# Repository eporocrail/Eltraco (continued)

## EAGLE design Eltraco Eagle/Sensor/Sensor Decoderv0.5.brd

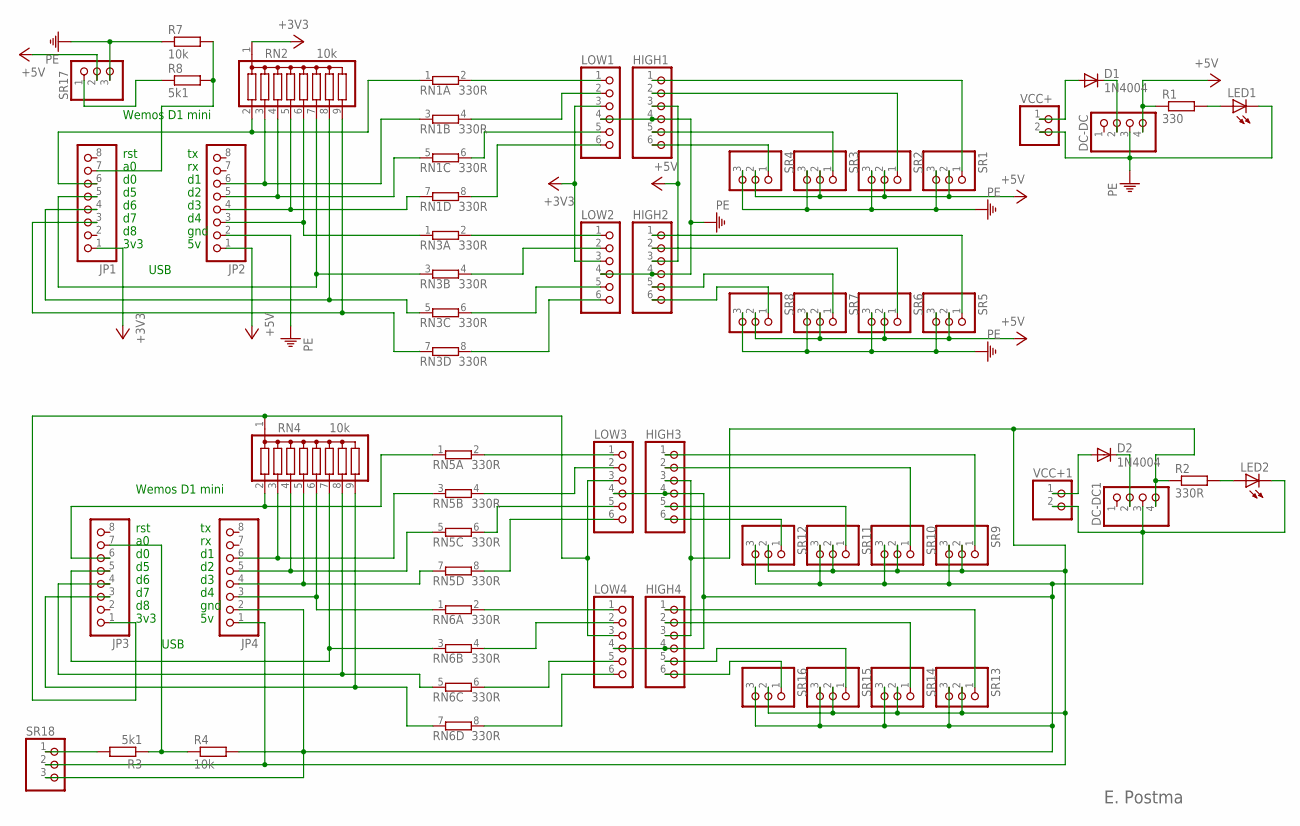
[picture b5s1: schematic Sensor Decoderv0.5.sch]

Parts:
D1, D2: 1N4004; DO41-10
DC-DC, DC-DC1: PINHD-1X4; 1X04
HIGH1, HIGH2, HIGH3, HIGH4: PINHD-1X6; 1X06
JP1, JP2, JP3, JP4: PINHD-1X8; 1X08
LED1, LED2: LED3MM
LOW1, LOW2, LOW3, LOW4: PINHD-1X6; 1X06
R1: 330; 0207/7
R2: 330R; 0207/7
R3, R8: 5k1; 0207/7
R4, R7: 10k; 0207/7
RN1, RN3, RN5, RN6: 330R; SIL8
RN2, RN4: 10k; SIL9
SR1, SR2, SR3, SR4, SR5, SR6, SR7, SR8, SR9, SR10, SR11, SR12, SR13, SR14, SR15, SR16, SR17, SR18: PINHD-1X3; 1X03
VCC+, VCC+1: PINHD-1X2; 1X02

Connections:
+3V3: JP1.1, LOW1.3, LOW2.3, RN2.1
+5V: DC-DC.4, HIGH1.3, HIGH2.3, JP2.1, R1.1, SR1.2, SR2.2, SR3.2, SR4.2, SR5.2, SR6.2, SR7.2, SR8.2, SR17.2
unnamed: HIGH2.6, SR8.1
unnamed: JP1.6, RN1.1, RN2.2
unnamed: JP1.4, RN2.8, RN3.5 (1)
unnamed: D1.C, DC-DC.2
unnamed: JP1.5, RN2.7, RN3.3 (1)
unnamed: LED1.A, R1.2
unnamed: JP2.5, RN1.5 (1), RN2.4
unnamed: HIGH2.5, SR7.1
unnamed: JP2.3, RN2.6, RN3.1
unnamed: JP2.6, RN1.3 (1), RN2.3
unnamed: JP1.3, RN2.9, RN3.7 (1)
unnamed: LOW1.1, RN1.2
unnamed: JP2.4, RN1.7 (1), RN2.5
unnamed: HIGH1.6, SR4.1
unnamed: HIGH1.5, SR3.1
unnamed: HIGH1.2, SR2.1
unnamed: HIGH1.1, SR1.1
unnamed: HIGH2.2, SR6.1
unnamed: HIGH2.1, SR5.1
unnamed: JP3.6, RN4.2, RN5.1
unnamed: LED2.A, R2.2
unnamed: JP4.6, RN4.3, RN5.3 (1)
unnamed: JP4.5, RN4.4, RN5.5 (1)
unnamed: JP4.4, RN4.5, RN5.7 (1)
unnamed: D2.A, VCC+1.1
unnamed: D2.C, DC-DC1.2
unnamed: JP4.3, RN4.6, RN6.1
unnamed: JP3.5, RN4.7, RN6.3 (1)
unnamed: JP3.4, RN4.8, RN6.5 (1)
unnamed: JP3.3, RN4.9, RN6.7 (1)
unnamed: LOW3.1, RN5.2
unnamed: LOW3.2, RN5.4 (2)
unnamed: LOW3.5, RN5.6 (2)
unnamed: LOW3.6, RN5.8 (2)
unnamed: LOW4.1, RN6.2
unnamed: LOW4.2, RN6.4 (2)
unnamed: LOW4.5, RN6.6 (2)
unnamed: LOW4.6, RN6.8 (2)
unnamed: HIGH4.6, SR16.1
unnamed: HIGH4.5, SR15.1
unnamed: HIGH4.2, SR14.1
unnamed: HIGH4.1, SR13.1
unnamed: HIGH3.6, SR12.1
unnamed: LOW1.2, RN1.4 (2)
unnamed: LOW1.5, RN1.6 (2)
unnamed: LOW1.6, RN1.8 (2)
unnamed: D1.A, VCC+.1
unnamed: LOW2.1, RN3.2
unnamed: LOW2.2, RN3.4 (2)
unnamed: LOW2.5, RN3.6 (2)
unnamed: LOW2.6, RN3.8 (2)
unnamed: HIGH3.5, SR11.1
unnamed: HIGH3.2, SR10.1
unnamed: HIGH3.1, SR9.1
unnamed: DC-DC1.4, HIGH3.3, HIGH4.3, JP4.1, R2.1, SR9.2, SR10.2, SR11.2, SR12.2, SR13.2, SR14.2, SR15.2, SR16.2, SR18.2
unnamed: JP3.1, LOW3.3, LOW4.3, RN4.1
unnamed: DC-DC1.3, HIGH3.4, HIGH4.4, JP4.2, LED2.K (C), LOW3.4, LOW4.4, R4.2, SR9.3, SR10.3, SR11.3, SR12.3, SR13.3, SR14.3, SR15.3, SR16.3, SR18.3, VCC+1.2
unnamed: JP1.7, R7.2, R8.2
unnamed: JP3.7, R3.1, R4.1
unnamed: R3.2, SR18.1
unnamed: R8.1, SR17.1
PE: DC-DC.3, HIGH1.4, HIGH2.4, JP2.2, LED1.K (C), LOW1.4, LOW2.4, R7.1, SR1.3, SR2.3, SR3.3, SR4.3, SR5.3, SR6.3, SR7.3, SR8.3, SR17.3, VCC+.2

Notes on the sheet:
rst
3v3
Wemos D1 mini
gnd
USB
E. Postma

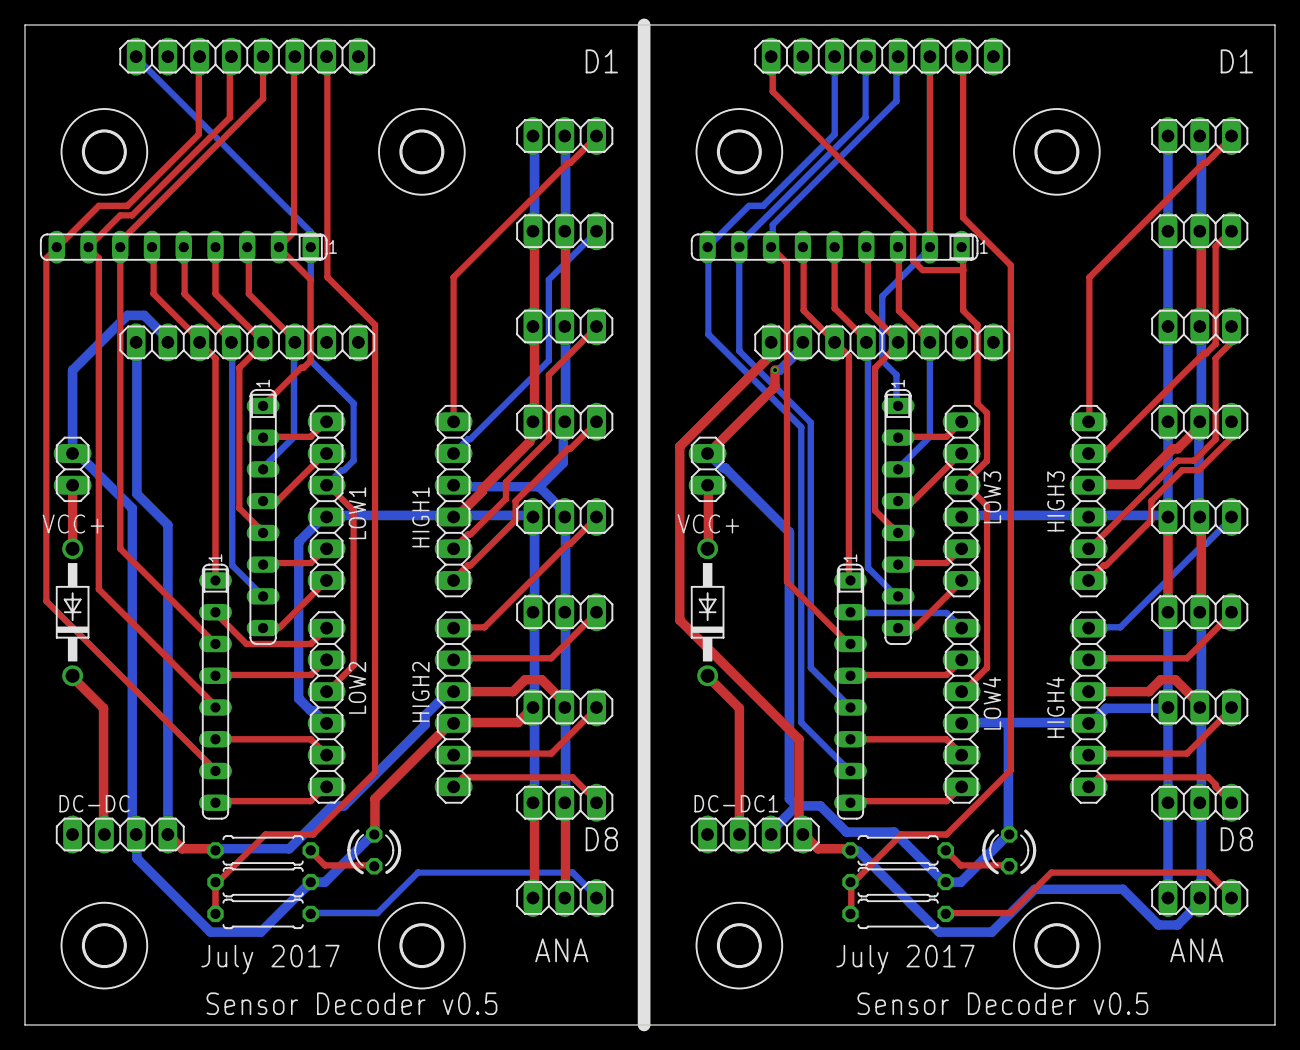
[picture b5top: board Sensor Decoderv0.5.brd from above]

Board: 2 copper layers, 100.0 x 80.0 mm, 58 parts (0 on the bottom side), 64 nets.

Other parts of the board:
U$1, U$2, U$3, U$4, U$5, U$6, U$7, U$8: 3,2

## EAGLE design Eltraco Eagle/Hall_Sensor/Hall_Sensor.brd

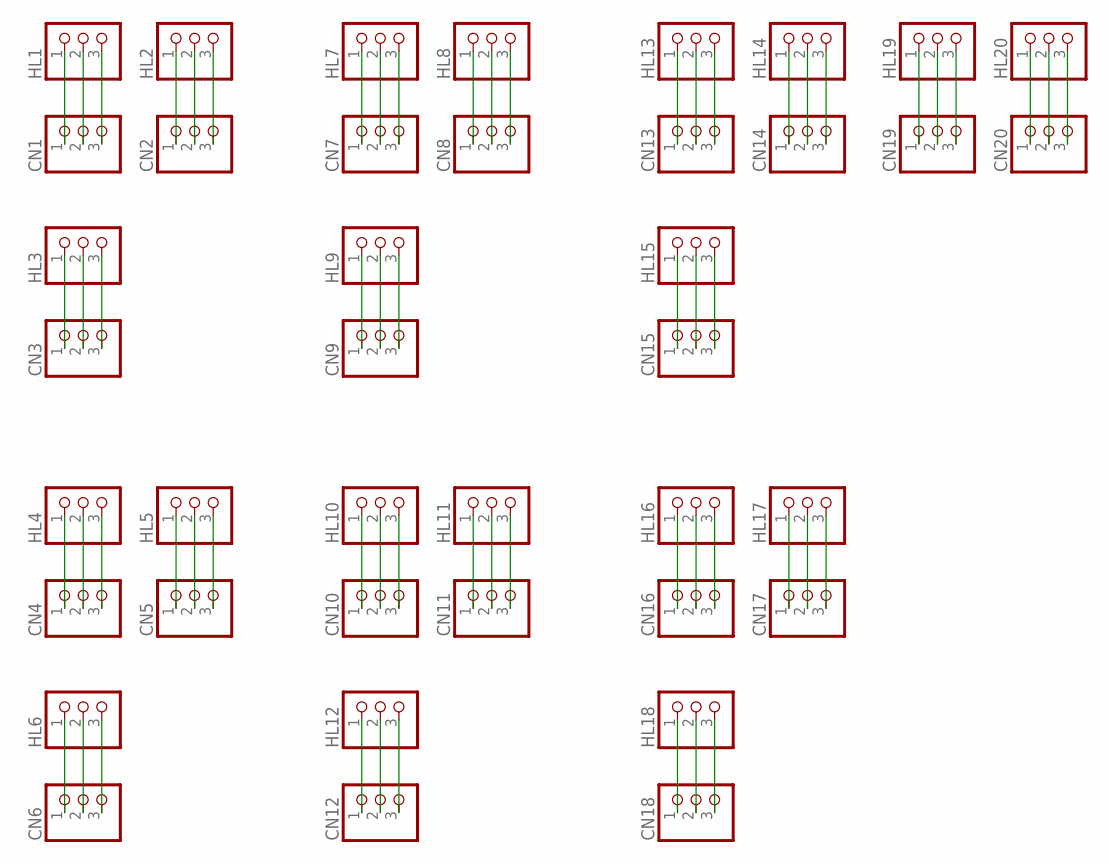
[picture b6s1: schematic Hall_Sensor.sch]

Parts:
CN1, CN2, CN3, CN4, CN5, CN6, CN7, CN8, CN9, CN10, CN11, CN12, CN13, CN14, CN15, CN16, CN17, CN18, CN19, CN20: PINHD-1X3; 1X03
HL1, HL2, HL3, HL4, HL5, HL6, HL7, HL8, HL9, HL10, HL11, HL12, HL13, HL14, HL15, HL16, HL17, HL18, HL19, HL20: PINHD-1X3; 1X03

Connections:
unnamed: CN7.1, HL7.1
unnamed: CN7.2, HL7.2
unnamed: CN7.3, HL7.3
unnamed: CN8.1, HL8.1
unnamed: CN8.2, HL8.2
unnamed: CN8.3, HL8.3
unnamed: CN9.1, HL9.1
unnamed: CN9.2, HL9.2
unnamed: CN9.3, HL9.3
unnamed: CN10.1, HL10.1
unnamed: CN10.2, HL10.2
unnamed: CN10.3, HL10.3
unnamed: CN11.1, HL11.1
unnamed: CN11.2, HL11.2
unnamed: CN11.3, HL11.3
unnamed: CN12.1, HL12.1
unnamed: CN12.2, HL12.2
unnamed: CN12.3, HL12.3
unnamed: CN13.1, HL13.1
unnamed: CN13.2, HL13.2
unnamed: CN13.3, HL13.3
unnamed: CN14.1, HL14.1
unnamed: CN14.2, HL14.2
unnamed: CN14.3, HL14.3
unnamed: CN15.1, HL15.1
unnamed: CN15.2, HL15.2
unnamed: CN15.3, HL15.3
unnamed: CN16.1, HL16.1
unnamed: CN16.2, HL16.2
unnamed: CN16.3, HL16.3
unnamed: CN17.1, HL17.1
unnamed: CN17.2, HL17.2
unnamed: CN17.3, HL17.3
unnamed: CN18.1, HL18.1
unnamed: CN18.2, HL18.2
unnamed: CN18.3, HL18.3
unnamed: CN19.1, HL19.1
unnamed: CN19.2, HL19.2
unnamed: CN19.3, HL19.3
unnamed: CN1.1, HL1.1
unnamed: CN20.1, HL20.1
unnamed: CN20.2, HL20.2
unnamed: CN20.3, HL20.3
unnamed: CN1.2, HL1.2
unnamed: CN1.3, HL1.3
unnamed: CN2.1, HL2.1
unnamed: CN2.2, HL2.2
unnamed: CN2.3, HL2.3
unnamed: CN3.1, HL3.1
unnamed: CN3.2, HL3.2
unnamed: CN3.3, HL3.3
unnamed: CN4.1, HL4.1
unnamed: CN4.2, HL4.2
unnamed: CN4.3, HL4.3
unnamed: CN5.1, HL5.1
unnamed: CN5.2, HL5.2
unnamed: CN5.3, HL5.3
unnamed: CN6.1, HL6.1
unnamed: CN6.2, HL6.2
unnamed: CN6.3, HL6.3

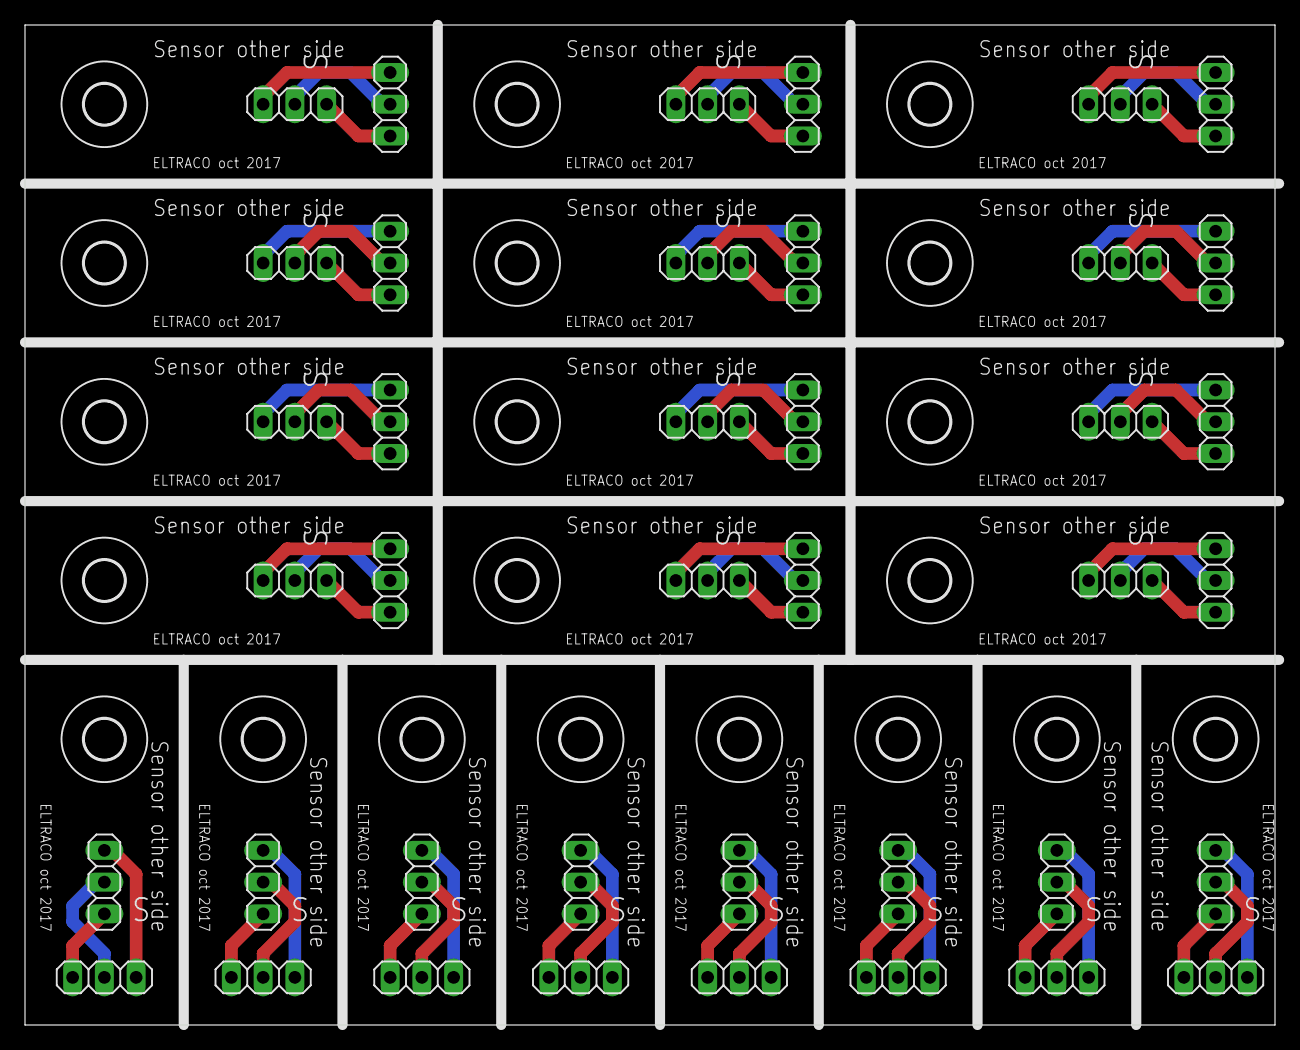
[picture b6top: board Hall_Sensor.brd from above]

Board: 2 copper layers, 100.0 x 80.0 mm, 60 parts (0 on the bottom side), 60 nets.

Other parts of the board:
U$1, U$2, U$3, U$4, U$5, U$6, U$7, U$8, U$9, U$10, U$11, U$12, U$13, U$14, U$15, U$16, U$17, U$18, U$19, U$20: 3,2

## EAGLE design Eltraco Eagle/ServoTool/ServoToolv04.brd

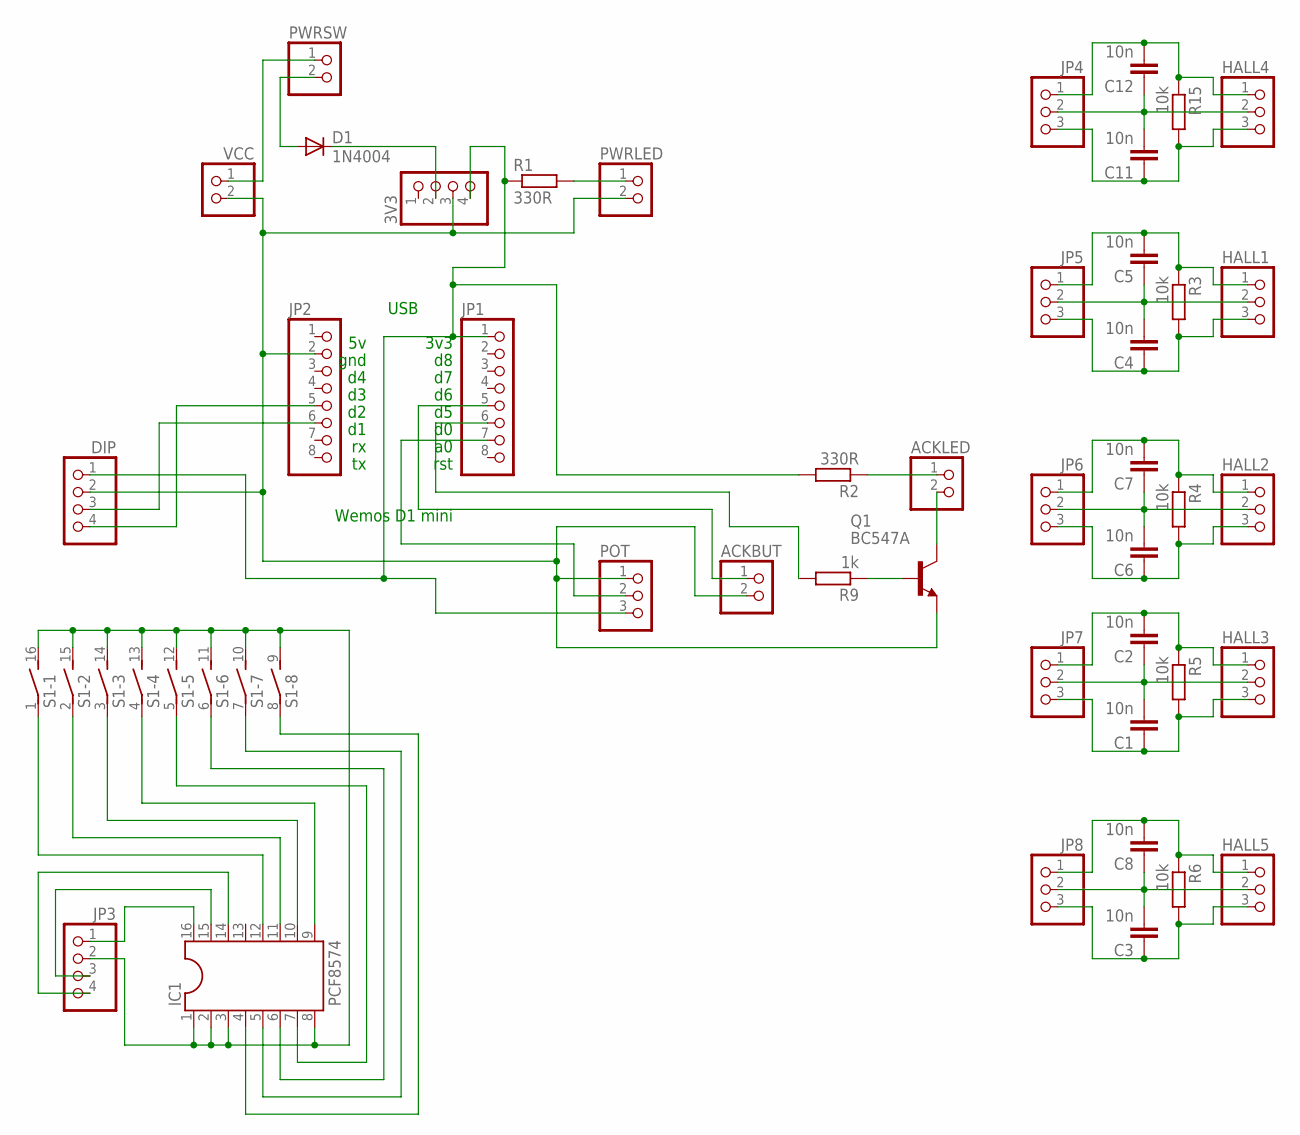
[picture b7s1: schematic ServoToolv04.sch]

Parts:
3V3: PINHD-1X4; 1X04
ACKBUT: PINHD-1X2/90; 1X02/90
ACKLED: PINHD-1X2/90; 1X02/90
C1, C2, C3, C4, C5, C6, C7, C8, C11, C12: 10n; C050-024X044
D1: 1N4004; DO41-10
DIP: PINHD-1X4/90; 1X04/90
HALL1, HALL2, HALL3, HALL4, HALL5: PINHD-1X3; 1X03
IC1: PCF8574; DIL16
JP1, JP2: PINHD-1X8; 1X08
JP3: PINHD-1X4/90; 1X04/90
JP4, JP5, JP6, JP7, JP8: PINHD-1X3; 1X03
POT: PINHD-1X3/90; 1X03/90
PWRLED: PINHD-1X2/90; 1X02/90
PWRSW: PINHD-1X2/90; 1X02/90
Q1: BC547A; TO92
R1, R2: 330R; 0207/10
R3, R4, R5, R6, R15: 10k; 0309/10
R9: 1k; 0207/10
S1: DIP08S
VCC: PINHD-1X2/90; 1X02/90

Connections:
unnamed: 3V3.4, DIP.1, JP1.1, POT.3, R1.1, R2.2
unnamed: DIP.3, JP2.6
unnamed: DIP.4, JP2.5
unnamed: 3V3.2, D1.C
unnamed: PWRSW.1, VCC.1
unnamed: PWRLED.1, R1.2
unnamed: Q1.2 (B), R9.1
unnamed: ACKLED.1, R2.1
unnamed: ACKLED.2, Q1.3 (C)
unnamed: IC1.12, S1.1
unnamed: IC1.11, S1.2 (1)
unnamed: IC1.10, S1.3 (1)
unnamed: IC1.16, JP3.1
unnamed: ACKBUT.1, JP1.5
unnamed: JP1.7, POT.2
unnamed: C5.2, HALL1.1, JP5.1, R3.1
unnamed: JP1.6, R9.2
unnamed: D1.A, PWRSW.2
unnamed: 3V3.3, ACKBUT.2, DIP.2, JP2.2, POT.1, PWRLED.2, Q1.1 (E), VCC.2
unnamed: C4.2, C5.1, HALL1.2, JP5.2
unnamed: IC1.1, IC1.2, IC1.3, IC1.8, JP3.2, S1.9 (2), S1.10 (2), S1.11 (2), S1.12 (2), S1.13 (2), S1.14 (2), S1.15 (2), S1.16 (2)
unnamed: IC1.15, JP3.3
unnamed: IC1.14, JP3.4
unnamed: IC1.9, S1.4 (1)
unnamed: IC1.7, S1.5 (1)
unnamed: IC1.6, S1.6 (1)
unnamed: C4.1, HALL1.3, JP5.3, R3.2
unnamed: C6.2, C7.1, HALL2.2, JP6.2
unnamed: IC1.5, S1.7 (1)
unnamed: C7.2, HALL2.1, JP6.1, R4.1
unnamed: C6.1, HALL2.3, JP6.3, R4.2
unnamed: C1.2, C2.1, HALL3.2, JP7.2
unnamed: C2.2, HALL3.1, JP7.1, R5.1
unnamed: C1.1, HALL3.3, JP7.3, R5.2
unnamed: IC1.4, S1.8 (1)
unnamed: C3.2, C8.1, HALL5.2, JP8.2
unnamed: C8.2, HALL5.1, JP8.1, R6.1
unnamed: C3.1, HALL5.3, JP8.3, R6.2
unnamed: C11.2, C12.1, HALL4.2, JP4.2
unnamed: C11.1, HALL4.3, JP4.3, R15.2
unnamed: C12.2, HALL4.1, JP4.1, R15.1

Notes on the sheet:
rst
3v3
Wemos D1 mini
gnd
USB

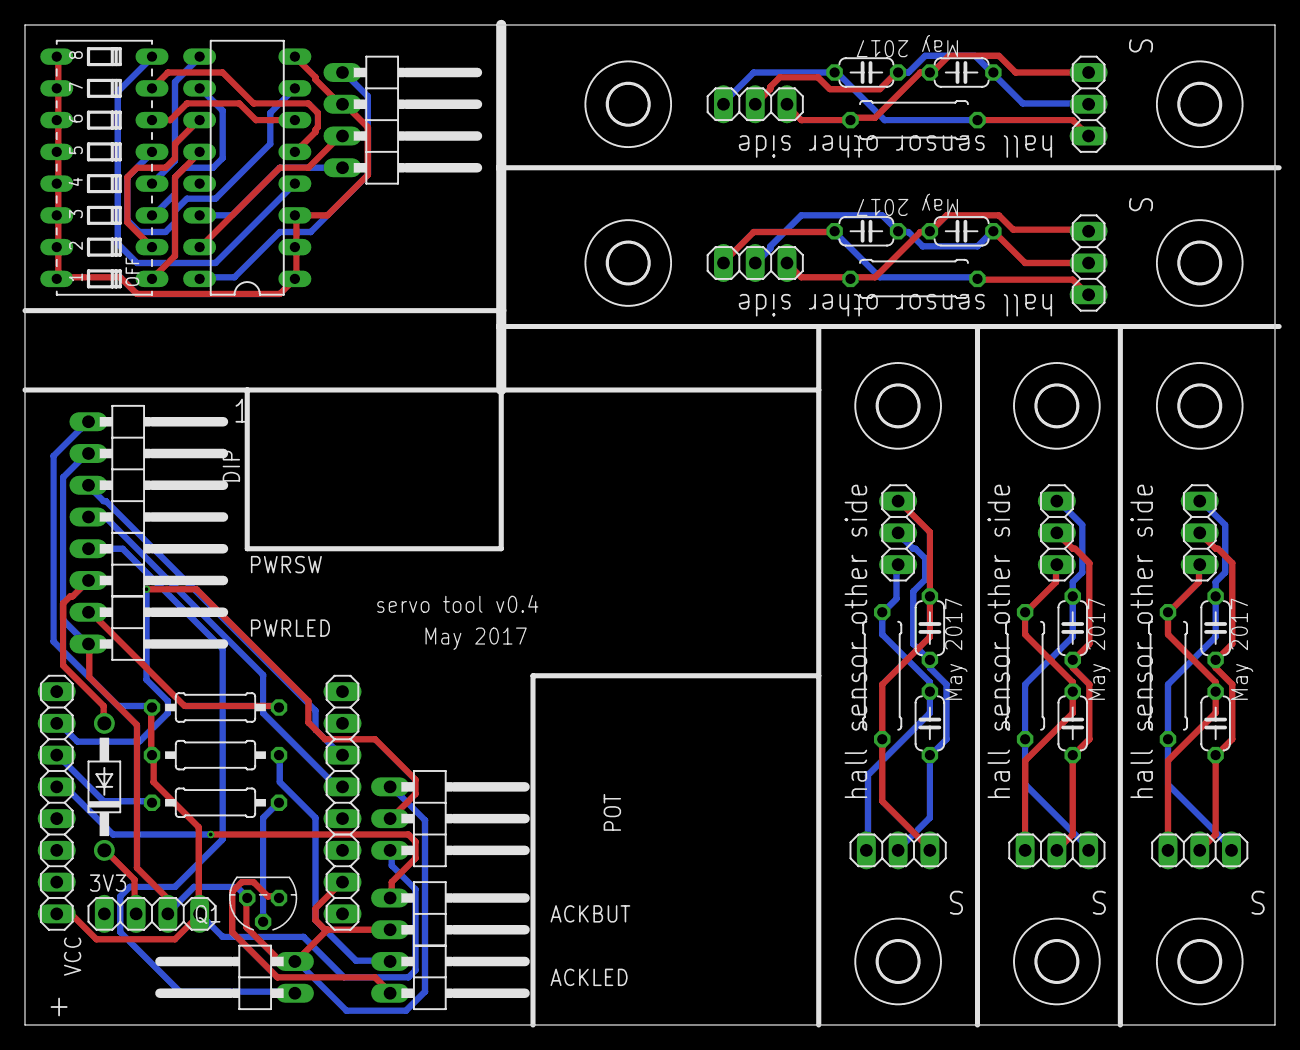
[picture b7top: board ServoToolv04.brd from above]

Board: 2 copper layers, 100.0 x 80.0 mm, 53 parts (0 on the bottom side), 41 nets.

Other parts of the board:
U$1, U$2, U$3, U$4, U$5, U$6, U$7, U$8, U$9, U$10: 3,2

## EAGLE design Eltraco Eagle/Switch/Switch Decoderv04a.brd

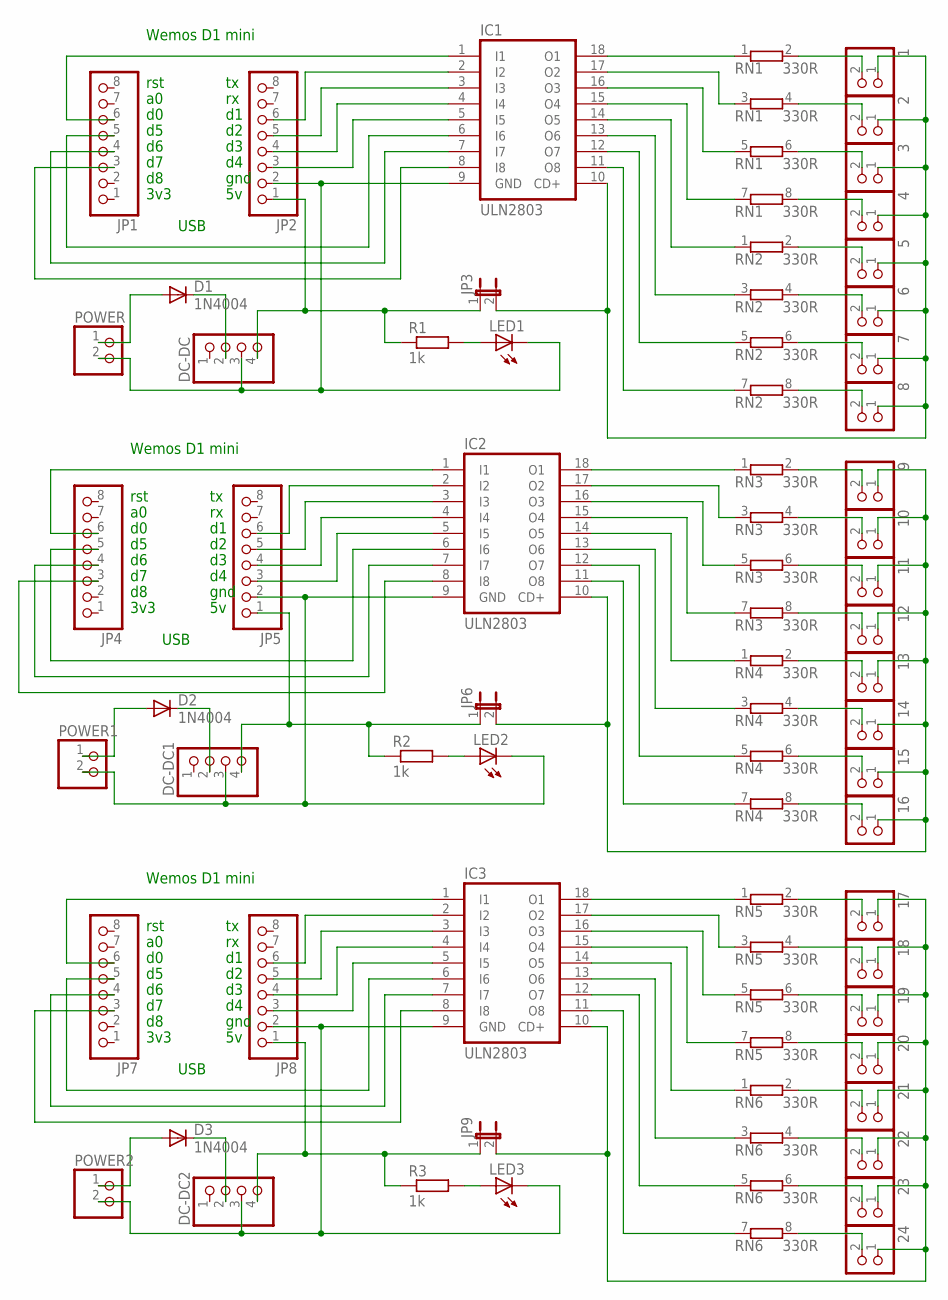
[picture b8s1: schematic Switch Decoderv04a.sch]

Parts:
1, 2, 3, 4, 5, 6, 7, 8, 9, 10, 11, 12, 13, 14, 15, 16, 17, 18, 19, 20, 21, 22, 23, 24: PINHD-1X2; 1X02
D1, D2, D3: 1N4004; DO41-10
DC-DC, DC-DC1, DC-DC2: PINHD-1X4; 1X04
IC1, IC2, IC3: ULN2803; DIL18
JP1, JP2, JP4, JP5, JP7, JP8: PINHD-1X8; 1X08
JP3, JP6, JP9: JP1E; JP1
LED1, LED2, LED3: LED3MM
POWER, POWER1, POWER2: PINHD-1X2; 1X02
R1, R2, R3: 1k; 0309/10
RN1, RN2, RN3, RN4, RN5, RN6: 330R; SIL8

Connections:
unnamed: DC-DC.3, IC1.9 (GND), JP2.2, LED1.K (C), POWER.2
unnamed: IC1.1 (I1), JP1.6
unnamed: IC1.7 (I7), JP1.4
unnamed: D1.C, DC-DC.2
unnamed: IC1.6 (I6), JP1.5
unnamed: LED1.A, R1.2
unnamed: IC1.3 (I3), JP2.5
unnamed: 1.1, 2.1, 3.1, 4.1, 5.1, 6.1, 7.1, 8.1, IC1.10 (CD+), JP3.2
unnamed: IC1.5 (I5), JP2.3
unnamed: IC1.2 (I2), JP2.6
unnamed: IC1.8 (I8), JP1.3
unnamed: IC1.18 (O1), RN1.1
unnamed: IC1.4 (I4), JP2.4
unnamed: IC2.1 (I1), JP4.6
unnamed: 1.2, RN1.2
unnamed: 9.1, 10.1, 11.1, 12.1, 13.1, 14.1, 15.1, 16.1, IC2.10 (CD+), JP6.2
unnamed: IC1.17 (O2), RN1.3 (1)
unnamed: 2.2, RN1.4 (2)
unnamed: 3.2, RN1.6 (2)
unnamed: IC1.16 (O3), RN1.5 (1)
unnamed: IC1.15 (O4), RN1.7 (1)
unnamed: 4.2, RN1.8 (2)
unnamed: 5.2, RN2.2
unnamed: IC1.14 (O5), RN2.1
unnamed: IC1.13 (O6), RN2.3 (1)
unnamed: 6.2, RN2.4 (2)
unnamed: 7.2, RN2.6 (2)
unnamed: IC1.12 (O7), RN2.5 (1)
unnamed: 8.2, RN2.8 (2)
unnamed: LED2.A, R2.2
unnamed: IC2.2 (I2), JP5.6
unnamed: IC2.3 (I3), JP5.5
unnamed: IC2.4 (I4), JP5.4
unnamed: D2.A, POWER1.1
unnamed: D2.C, DC-DC1.2
unnamed: IC2.5 (I5), JP5.3
unnamed: IC2.6 (I6), JP4.5
unnamed: IC2.7 (I7), JP4.4
unnamed: IC2.8 (I8), JP4.3
unnamed: IC3.18 (O1), RN5.1
unnamed: DC-DC1.3, IC2.9 (GND), JP5.2, LED2.K (C), POWER1.2
unnamed: IC1.11 (O8), RN2.7 (1)
unnamed: IC2.11 (O8), RN4.7 (1)
unnamed: IC2.18 (O1), RN3.1
unnamed: IC2.17 (O2), RN3.3 (1)
unnamed: 9.2, RN3.2
unnamed: D1.A, POWER.1
unnamed: 10.2, RN3.4 (2)
unnamed: IC2.16 (O3), RN3.5 (1)
unnamed: IC2.15 (O4), RN3.7 (1)
unnamed: 11.2, RN3.6 (2)
unnamed: 12.2, RN3.8 (2)
unnamed: IC2.14 (O5), RN4.1
unnamed: IC2.13 (O6), RN4.3 (1)
unnamed: 13.2, RN4.2
unnamed: 14.2, RN4.4 (2)
unnamed: IC2.12 (O7), RN4.5 (1)
unnamed: 15.2, RN4.6 (2)
unnamed: IC3.1 (I1), JP7.6
unnamed: LED3.A, R3.2
unnamed: IC3.2 (I2), JP8.6
unnamed: IC3.3 (I3), JP8.5
unnamed: IC3.4 (I4), JP8.4
unnamed: D3.A, POWER2.1
unnamed: D3.C, DC-DC2.2
unnamed: IC3.5 (I5), JP8.3
unnamed: IC3.6 (I6), JP7.5
unnamed: IC3.7 (I7), JP7.4
unnamed: IC3.8 (I8), JP7.3
unnamed: 17.1, 18.1, 19.1, 20.1, 21.1, 22.1, 23.1, 24.1, IC3.10 (CD+), JP9.2
unnamed: DC-DC2.3, IC3.9 (GND), JP8.2, LED3.K (C), POWER2.2
unnamed: 16.2, RN4.8 (2)
unnamed: IC3.11 (O8), RN6.7 (1)
unnamed: DC-DC.4, JP2.1, JP3.1, R1.1
unnamed: IC3.17 (O2), RN5.3 (1)
unnamed: DC-DC1.4, JP5.1, JP6.1, R2.1
unnamed: DC-DC2.4, JP8.1, JP9.1, R3.1
unnamed: IC3.16 (O3), RN5.5 (1)
unnamed: IC3.15 (O4), RN5.7 (1)
unnamed: 17.2, RN5.2
unnamed: IC3.14 (O5), RN6.1
unnamed: IC3.13 (O6), RN6.3 (1)
unnamed: 18.2, RN5.4 (2)
unnamed: 19.2, RN5.6 (2)
unnamed: IC3.12 (O7), RN6.5 (1)
unnamed: 20.2, RN5.8 (2)
unnamed: 21.2, RN6.2
unnamed: 22.2, RN6.4 (2)
unnamed: 23.2, RN6.6 (2)
unnamed: 24.2, RN6.8 (2)

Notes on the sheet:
rst
3v3
Wemos D1 mini
gnd
USB

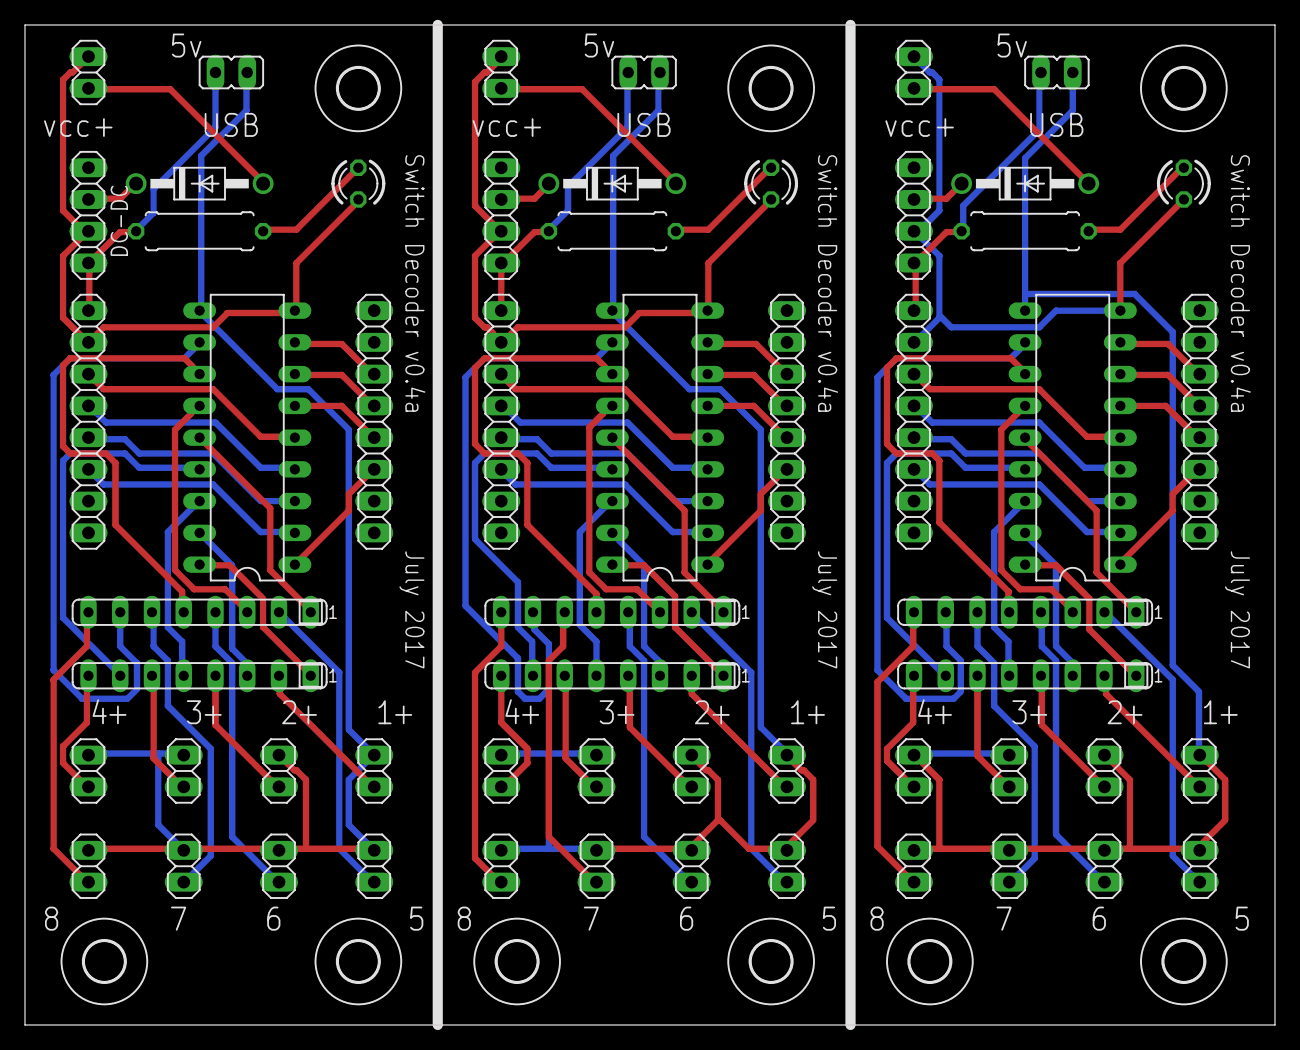
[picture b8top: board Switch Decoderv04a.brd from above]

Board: 2 copper layers, 100.0 x 80.0 mm, 66 parts (0 on the bottom side), 90 nets.

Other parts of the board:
U$1, U$2, U$3, U$4, U$5, U$6, U$7, U$8, U$9: 3,2

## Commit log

2017-10-01 Sensor decoder
    Working version of the sensor decoder. Eight digital and one analogue
    sensors signal occupancy to Rocrail. Available sensors are hall sensor
    and single current detector sensor.
2017-10-01 Summary Eltraco
2017-10-01 Extra available info
2017-10-01 Adjusted layout
2017-10-01 Eagle files for Eltraco
2017-10-02 DCC++ booster running on Arduino Nano
    The original software has been adapted to run on Arduino Nano with
    related motor shield.
    The aim is to operate this booster via WiFi and MQTT.
2017-10-23 Eagles files for hall sensor connector
2017-12-11 Qos2 Publishing
    New library with qos2 implemented.
    Byte changed into char.
    yield() in loop.
    Length of MQTT outgoing message equal to Rocnet message length.
    Display of published and received messages on serial monitor harmonised.
2017-12-12 Receiver for MQTT messages
    Tool for developing Eltraco software
2017-12-13 Fast Clock module synchronised by Rocrail
    0.6 inch Oled display with analogue clock
2017-12-19 MQTT broker details retrieved from Rocrail or default data used
    Liviu developed a software module to retrieve MQTT broker data from
    Rocrail. This module is slightly adapted and incorporated.
2017-12-20 Replace "char" by "byte" for numbers
2017-12-22 Software version display added with internal clean-up
    Software versioning has changed. Display of current version on serial
    monitor. Internal clean-up.
2018-01-03 Incoming switch order now correct
    Wrong byte of incoming payload corrected.
2018-01-04 One of two no PCB traces. Corrected.
2018-02-08 Major change in software
    The separate software packages have been combined into one Eltraco
    package. Configuration is done by means of the built-in “Eltraco
    configuration website”. Servo adjustment is done via the same website.
    The “servo tool” is abandonned.
    Further more a new decoder is introduced, the single turnout decoder
    with four connectors for external sensors.
2018-02-08 Minor detail corrected
2018-02-08 Minor correction
2018-02-08 ESP8266WebServer server(80); inserted
    ESP8266WebServer server = ESP8266WebServer(80); replaced by
    ESP8266WebServer server(80);
2018-02-08 "Only last triplet of IP-address" added on configuration webpage
2018-02-09 Ref to different software packages removed
2018-02-09 New version PCB files and extra PCBs
    Value of components printed on PCB. Current sensor, hall sensor and
    relais add-on PCB added
2018-02-10 Cosmetic change on serial monitor
    Aligned display of SPIFFS content better
2018-02-11 Reboot inserted after "wifi restart" selection in configuration webpage
2018-02-13 Serial monitor messages harmonised
2018-02-14 FTP server added; display of debug messages enhanced
    FTP server provides a fast way to upload files to SPIFFS. Code to
    display debug messages on serial display optimised.
2018-02-15 Updated page outlook
2018-02-15 Fixed processing web message for debug and wifi manager flag
2018-02-15 Behaviour web pages optimised
2018-02-15 Web page "servo adjustment" updated
2018-04-03 "Fault publishing" displayed only once. Stray angle "255" blocked from being processed.
2018-04-06 Incorporation off minimum positive scan pulse duration of 300 milllis
    The Hall sensor generates a puls of only several ms. This is to short
    for Rocrail. Every positive scan pulse is has now an adjustable
    duration. Default is 300 ms.
2018-08-20 Example using the EmbAJAX library
    EmbAJAX provides capabilities to create interactive webpages on an
    ESP8266 module.
2018-12-26 Completely overhauled version
    Structure of software changed completely. EMBajax implemented. Each
    decoder has its own configuration website. One package four decoders.
    New functionality separate software package.
